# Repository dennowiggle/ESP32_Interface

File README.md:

# ESP32_Interface
Facilitate learning the Z80 Retro! hardware and software.

## Feature list:
ESP32-s3 based board to provide WiFi enabled features.
* RS232 connection to main Z80-Retro console via cable for telnet console access
* RS232 connection to Z80-Retro Aux com port via cable for future WiFi enabled serial download.
* Z80 bus programmer using MCP23S17 SPI IO expander devices.
  - facilitates faster Z80 bus access at 10Mhz SPI rate. 
    - Serial access still relatively slow but 25x I2C.
  - Program Flash without the need for a Raspberry Pi.
  - Might be possible to program areas of SRAM memory e.g. future WiFi file download.
* Off-board SPI using header connection to future board(s) such as FPGA video card.
  - programming FPGA plus additional SPI-FPGA debug features if needed.
* One byte, 8 bit, message register implemented in logic for handshaking with Z80.
  - uses IORQ addreess line 0xA4.
* USB OTG is present in hardware.
* SD card slot for future possiblities.

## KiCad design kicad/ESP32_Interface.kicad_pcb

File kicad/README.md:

# ESP32_Interface
Facilitate learning the Z80 Retro! hardware and software.

## Description
This project adds a WiFi interface to the Z80 Retro! It has been used to facilitate telnet to the Z80 serial port, and programming the Z80 Retro! Flash memory via serial or telnet xmodem or a web interface.

## Top View

## Bottom View

## ESP32 Interface Board Rev 1.0 Release Notes

1. The 'output' directory contains the BOM, netlist, and PDF schematic.

2. Board design used KiCad 7.0.2.

3. Silkscreen box on back side should extend around R501.

4. Holes for U505, the ESP32 module, are tight but it is possible to fit the module in. Larger pin holes would be preferred.

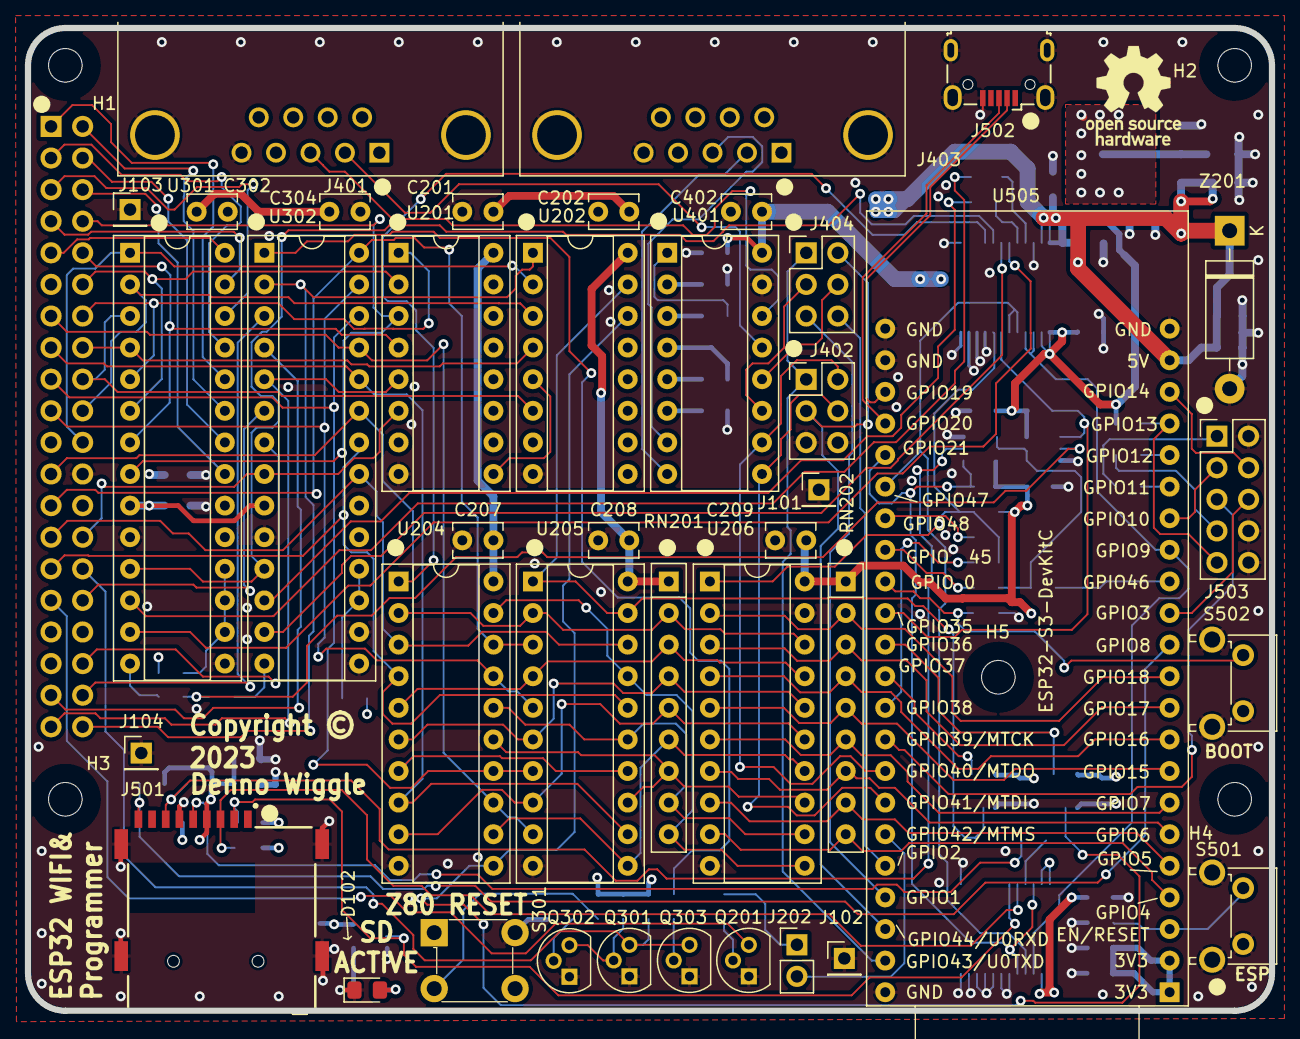
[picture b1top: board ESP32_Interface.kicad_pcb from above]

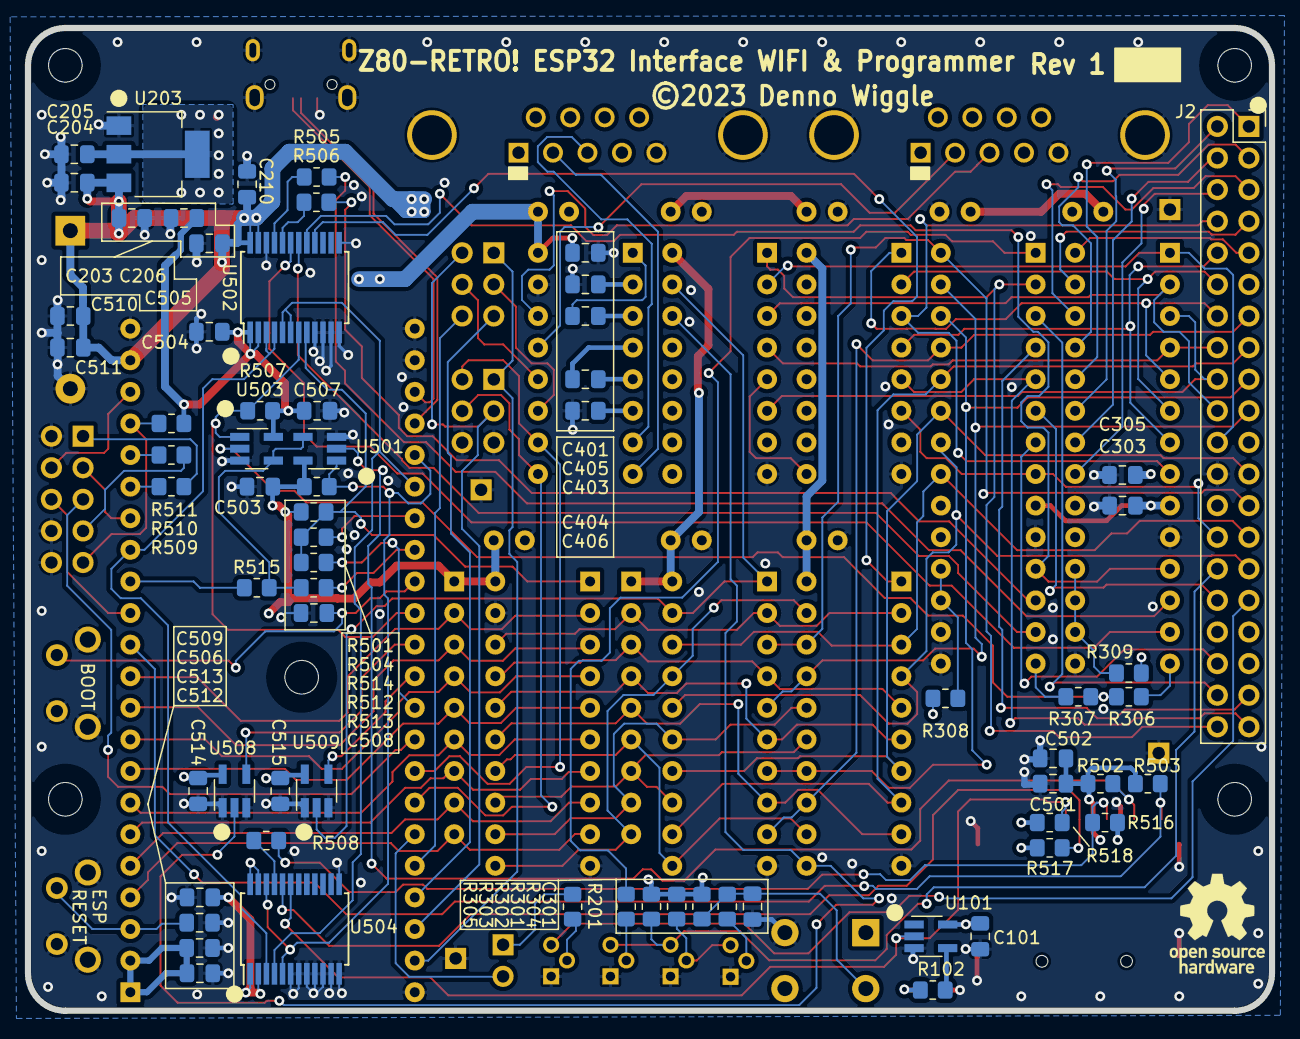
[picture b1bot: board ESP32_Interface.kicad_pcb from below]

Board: 4 copper layers, 100.0 x 79.0 mm, 114 parts (68 on the bottom side), 128 nets.

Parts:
C101, C204, C205, C403, C404, C405, C406, C501, C503, C504, C505, C506, C507, C509, C510, C512, C514, C515: 100nF; C_0805_2012Metric_Pad1.18x1.45mm_HandSolder
C201, C202, C207, C208, C209, C302, C304, C402: 100n; C_Disc_D3.8mm_W2.6mm_P2.50mm
C203, C206, C210, C301, C303, C305, C401, C502, C511, C513: 10uF; C_0805_2012Metric_Pad1.18x1.45mm_HandSolder
C508: DNL; C_0805_2012Metric_Pad1.18x1.45mm_HandSolder
D102: LTST-C170KGKT; LED_0805_2012Metric_Pad1.15x1.40mm_HandSolder
H1, H2, H3, H4, H5: MountingHole; MountingHole_2.7mm_M2.5_DIN965
J2: Conn_02x20_Counter_Clockwise; PinSocket_2x20_P2.54mm_Vertical_clockwise
J101, J102, J103, J104: Conn_01x01; PinHeader_1x01_P2.54mm_Vertical
J202: Conn_01x02; PinHeader_1x02_P2.54mm_Vertical
J401, J403: DB9_Male_MountingHoles; DSUB-9_Male_Horizontal_P2.77x2.84mm_EdgePinOffset7.70mm_Hou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
J402, J404: Conn_02x03; PinHeader_2x03_P2.54mm_Vertical
J501: GCT_MEM2075-00-140-01-A_DP; GCT_MEM2075-00-140-01-A
J502: USB_B_Micro; USB_Micro-B_Wuerth_629105150521
J503: Conn_02x05; PinHeader_2x05_P2.54mm_Vertical
LOGO10, LOGO11: Logo_Open_Hardware_Small; OSHW-Logo_7.5x8mm_SilkScreen
Q201, Q301, Q302, Q303: PN2222; TO-92L
R102, R201, R305: 1K; R_0805_2012Metric_Pad1.20x1.40mm_HandSolder
R301, R302, R303, R308, R309, R501, R502, R503, R504, R507, R511, R516, R517, R518: 10K; R_0805_2012Metric_Pad1.20x1.40mm_HandSolder
R304: 47K; R_0805_2012Metric_Pad1.20x1.40mm_HandSolder
R306, R307, R505, R506, R508, R509, R510: 33R; R_0805_2012Metric_Pad1.20x1.40mm_HandSolder
R512, R513: 0R; R_0805_2012Metric_Pad1.20x1.40mm_HandSolder
R514, R515: DNL; R_0805_2012Metric_Pad1.20x1.40mm_HandSolder
RN201, RN202: 10K; R_Array_SIP9
S301: 1825910-6; Switch_Tactile_THT_6x6mm
S501: 1-1825027-2; SW_Tactile_SPST_Angled_PTS645Vx83-2LFS
S502: 1825027-8; SW_Tactile_SPST_Angled_PTS645Vx83-2LFS
U101: SN74LVC1G04DBVR; SOT-23-5_HandSoldering
U201, U202: 74LS138; DIP-16_W7.62mm_Socket
U203: NCP1117LPST33T3G; SOT-223
U204: 74HC374; DIP-20_W7.62mm_Socket
U205: 74LS244; DIP-20_W7.62mm_Socket
U206: 74LVC245A; DIP-20_W7.62mm_Socket
U301, U302: MCP23S17_SP; DIP-28_W7.62mm_Socket
U401: ICL3232CPZ; DIP-16_W7.62mm_Socket
U501, U503, U508, U509: SN74LVC1G125DBVR; SOT-23-5_HandSoldering
U502, U504: SN74LVC8T245DBR; SSOP-24_5.3x8.2mm_P0.65mm
U505: ESP32-S3-DevKitC
Z201: SA5.0A; D_DO-15_P12.70mm_Horizontal

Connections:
+3.3V: C101.1, C205.1, C206.1, C209.1, C401.1, C402.1, C501.1, C502.1, C503.1, C504.1, C507.1, C509.1, C514.1, C515.1, J501.4 (VDD), R501.1, R502.1, R503.1, R504.1, R507.1, R511.1, R516.1, R517.1, R518.1, RN202.1 (common), U101.5 (VCC), U203.2 (OUT), U203.4 (OUT), U206.20 (Vcc), U401.16 (VCC), U501.5 (VCC), U502.1 (VCCA), U502.2 (DIR), U503.5 (VCC), U504.1 (VCCA), U504.2 (DIR), U504.23 (VCCB), U504.24 (VCCB), U508.5 (VCC), U509.5 (VCC)
+3.3VP: C512.1, C513.1, U505.1 (3V3), U505.2 (3V3)
+5V: C201.1, C202.1, C203.1, C204.1, C207.1, C208.1, C210.1, C302.1, C303.1, C304.1, C305.1, C505.1, C510.1, C511.1, J2.11, R301.1, R302.1, R303.1, R308.1, R309.1, RN201.1 (common), U201.16 (VCC), U202.16 (VCC), U203.3 (IN), U204.20 (VCC), U205.20 (VCC), U301.9 (VDD), U302.9 (VDD), U502.23 (VCCB), U502.24 (VCCB), U505.21 (5V), Z201.1
/ESP32/AUX_DONE: J503.6, U505.13 (GPIO3/ADC1_CH2)
/ESP32/AUX_SPI_CLK: J503.7, R510.2
/ESP32/AUX_SPI_CLK_S: R510.1, U505.18 (GPIO12/ADC2_CH1)
/ESP32/AUX_SPI_MISO: J503.9, R511.2, U505.19 (GPIO13/ADC2_CH2)
/ESP32/AUX_SPI_MOSI: J503.1, R509.2
/ESP32/AUX_SPI_MOSI_S: R509.1, U505.17 (GPIO11/ADC2_CH0)
/ESP32/DATA_DIR_38: R512.1, U505.35 (GPIO38)
/ESP32/DATA_DIR_48: R514.1, U505.29 (GPIO48)
/ESP32/ESP_SD_DET: J501.9 (~DET), R503.2, U505.12 (GPIO8/ADC1_CH7)
/ESP32/ESP_SPI_CLK: U502.3 (A1), U502.4 (A2), U504.3 (A1), U505.15 (GPIO9/ADC1_CH8)
/ESP32/ESP_SPI_MISO: R513.2, R515.2, U501.4 (Y), U503.4 (Y)
/ESP32/ESP_SPI_MISO_IO45: R513.1, U505.30 (GPIO45)
/ESP32/ESP_SPI_MISO_IO46: R515.1, U505.14 (GPIO46)
/ESP32/ESP_SPI_MOSI: U502.5 (A3), U502.6 (A4), U504.4 (A2), U505.28 (GPIO47)
/ESP32/S1ACK: R505.1, U502.21 (B1)
/ESP32/S1BCK: R506.1, U502.20 (B2)
/ESP32/SPI_SD_CLK: J501.5 (CLK), R508.2, R516.2
/ESP32/SPI_SD_MISO: J501.7 (DAT0), R502.2, U501.2 (A)
/ESP32/SPI_SD_MOSI: J501.3 (CMD), R517.2, U504.20 (B2)
/ESP32/SSDCK: R508.1, U504.21 (B1)
/ESP32/USB_OTG_JTAG_D+: J502.3 (D+), U505.26 (GPIO20/USB_D+)
/ESP32/USB_OTG_JTAG_D-: J502.2 (D-), U505.25 (GPIO19/USB_D-)
/ESP32/~AUX_RESET: J503.5, U505.36 (GPIO39/MTCK)
/ESP32/~AUX_SPI_CS0: J503.3, U505.16 (GPIO10/ADC1_CH9)
/ESP32/~AUX_SPI_CS1: J503.4, U505.20 (GPIO14/ADC2_CH3)
/ESP32/~BIORQ_A4_RD: U505.34 (GPIO37), U509.4 (Y)
/ESP32/~BIORQ_A4_WR: U505.33 (GPIO36), U508.4 (Y)
/ESP32/~BOOT: C508.1, S502.1, U505.31 (GPIO0)
/ESP32/~ESP_RESET: C506.1, S501.1, U505.3 (CHIP_PU)
/ESP32/~ESP_SPI_CS0: R501.2, U501.1 (~OE), U504.5 (A3), U504.22 (OE), U505.27 (GPIO21)
/ESP32/~ESP_SPI_CS1: R507.2, U502.7 (A5), U503.1 (~OE), U505.32 (GPIO35)
/RS232/RS232_DOWNLOAD_RX: J401.2, U401.13 (R1IN)
/RS232/RS232_DOWNLOAD_TX: J401.3, U401.14 (T1OUT)
/RS232/RS232_Z80_RX: J403.2, U401.8 (R2IN)
/RS232/RS232_Z80_TX: J403.3, U401.7 (T2OUT)
/RS232/UART01_RX: J404.4, U401.12 (R1OUT)
/RS232/UART01_TX: J404.3, U401.11 (T1IN)
/SPI<->Z80 Bus/ADD_1A: R309.2, U301.16 (A1), U301.17 (A2), U301.18 (~RESET)
/SPI<->Z80 Bus/ADD_1B: R308.2, U302.17 (A2), U302.18 (~RESET)
/SPI<->Z80 Bus/SPI_1A_MISO: R306.1, U301.14 (SO)
/SPI<->Z80 Bus/SPI_1B_MISO: R307.1, U302.14 (SO)
/Z80 Retro Interface/BD0: RN201.2 (R1), U204.2 (O0), U205.2 (I0a), U206.18 (B1)
/Z80 Retro Interface/BD1: RN201.3 (R2), U204.5 (O1), U205.4 (I1a), U206.17 (B2)
/Z80 Retro Interface/BD2: RN201.4 (R3), U204.6 (O2), U205.6 (I2a), U206.16 (B3)
/Z80 Retro Interface/BD3: RN201.5 (R4), U204.9 (O3), U205.8 (I3a), U206.15 (B4)
/Z80 Retro Interface/BD4: RN201.6 (R5), U204.12 (O4), U205.11 (I0b), U206.14 (B5)
/Z80 Retro Interface/BD5: RN201.7 (R6), U204.15 (O5), U205.13 (I1b), U206.13 (B6)
/Z80 Retro Interface/BD6: RN201.8 (R7), U204.16 (O6), U205.15 (I2b), U206.12 (B7)
/Z80 Retro Interface/BD7: RN201.9 (R8), U204.19 (O7), U205.17 (I3b), U206.11 (B8)
/Z80 Retro Interface/~INT: J2.16, Q201.3 (C)
/Z80 Retro Interface/~IORQ_AX: U201.9 (O6), U202.5 (E2)
A0: J2.30, U202.2 (A1), U301.1 (GPB0)
A1: J2.31, U202.3 (A2), U301.2 (GPB1)
A2: J2.32, U202.6 (E3), U301.3 (GPB2)
A3: J2.33, U202.4 (E1), U301.4 (GPB3)
A4: J2.34, U201.1 (A0), U301.5 (GPB4)
A5: J2.35, U201.2 (A1), U301.6 (GPB5)
A6: J2.36, U201.4 (E1), U301.7 (GPB6)
A7: J2.37, U201.3 (A2), U301.8 (GPB7)
A8: J2.38, U301.21 (GPA0)
A9: J2.39, U301.22 (GPA1)
A10: J2.40, U301.23 (GPA2)
A11: J2.1, U301.24 (GPA3)
A12: J2.2, U301.25 (GPA4)
A13: J2.3, U301.26 (GPA5)
A14: J2.4, U301.27 (GPA6)
A15: J2.5, U301.28 (GPA7)
D0: J2.14, U204.3 (D0), U205.18 (O0a), U302.21 (GPA0)
D1: J2.15, U204.4 (D1), U205.16 (O1a), U302.22 (GPA1)
D2: J2.12, U204.7 (D2), U205.14 (O2a), U302.23 (GPA2)
D3: J2.8, U204.8 (D3), U205.12 (O3a), U302.24 (GPA3)
D4: J2.7, U204.13 (D4), U205.9 (O0b), U302.25 (GPA4)
D5: J2.9, U204.14 (D5), U205.7 (O1b), U302.26 (GPA5)
D6: J2.10, U204.17 (D6), U205.5 (O2b), U302.27 (GPA6)
D7: J2.13, U204.18 (D7), U205.3 (O3b), U302.28 (GPA7)
ESP_D0: RN202.2 (R1), U206.2 (A1), U505.11 (GPIO18/ADC2_CH7)
ESP_D1: RN202.3 (R2), U206.3 (A2), U505.10 (GPIO17/ADC2_CH6)
ESP_D2: RN202.4 (R3), U206.4 (A3), U505.9 (GPIO16/ADC2_CH5/32K_N)
ESP_D3: RN202.5 (R4), U206.5 (A4), U505.8 (GPIO15/ADC2_CH4/32K_P)
ESP_D4: RN202.6 (R5), U206.6 (A5), U505.7 (GPIO7/ADC1_CH6)
ESP_D5: RN202.7 (R6), U206.7 (A6), U505.6 (GPIO6/ADC1_CH5)
ESP_D6: RN202.8 (R7), U206.8 (A7), U505.5 (GPIO5/ADC1_CH4)
ESP_D7: RN202.9 (R8), U206.9 (A8), U505.4 (GPIO4/ADC1_CH3)
ESP_DATA_DIR5_W: U204.1 (OE), U502.16 (B6)
ESP_DATA_DIR_W: R504.2, R512.2, R514.2, U206.1 (DIR), U502.8 (A6)
GND: C101.2, C201.2, C202.2, C203.2, C204.2, C205.2, C206.2, C207.2, C208.2, C209.2, C210.2, C301.2, C302.2, C303.2, C304.2, C305.2, C401.2, C402.2, C405.2, C406.2, C501.2, C502.2, C503.2, C504.2, C505.2, C506.2, C507.2, C508.2, C509.2, C510.2, C511.2, C512.2, C513.2, C514.2, C515.2, D102.1, J2.29, J101.1, J102.1, J103.1, J104.1, J401.0 (PAD), J401.5, J402.5, J402.6, J403.0 (PAD), J403.5, J501.6 (VSS), J501.SH1 (SHIELD), J501.SH2 (SHIELD), J501.SH3 (SHIELD), J501.SH4 (SHIELD), J502.5 (GND), J502.6 (Shield), J503.2, J503.8, J503.10, Q201.1 (E), Q301.1 (E), Q302.1 (E), Q303.1 (E), S301.2, S501.2, S501.SH1, S501.SH2, S502.2, S502.SH1, S502.SH2, U101.3 (GND), U201.8 (GND), U202.8 (GND), U203.1 (ADJ/GND), U204.10 (GND), U205.10 (GND), U206.10 (GND), U206.19 (OE), U301.10 (VSS), U301.15 (A0), U302.10 (VSS), U302.15 (A0), U302.16 (A1), U401.15 (GND), U501.3 (GND), U502.9 (A7), U502.10 (A8), U502.11 (GND), U502.12 (GND), U502.13 (GND), U502.22 (OE), U503.3 (GND), U504.6 (A4), U504.7 (A5), U504.8 (A6), U504.9 (A7), U504.10 (A8), U504.11 (GND), U504.12 (GND), U504.13 (GND), U505.22 (GND), U505.23 (GND), U505.24 (GND), U505.44 (GND), U508.1 (~OE), U508.3 (GND), U509.1 (~OE), U509.3 (GND), Z201.2
unnamed: C301.1, R301.2, R304.1, S301.3
unnamed: D102.2, R102.2
unnamed: J202.1, R201.2
unnamed: Q201.2 (B), R201.1
unnamed: Q301.2 (B), Q302.3 (C), R302.2
unnamed: Q302.2 (B), R304.2
unnamed: Q303.2 (B), R305.2
unnamed: R102.1, U101.4 (Y)
unnamed: R305.1, U302.1 (GPB0)
unnamed: C403.2, U401.1 (C1+)
unnamed: C403.1, U401.3 (C1-)
unnamed: C404.1, U401.4 (C2+)
unnamed: C404.2, U401.5 (C2-)
unnamed: C405.1, U401.2 (VS+)
unnamed: C406.1, U401.6 (VS-)
SPI_1A_CLK: R505.2, U301.12 (SCK)
SPI_1A_MOSI: U301.13 (SI), U502.19 (B3)
SPI_1B_CLK: R506.2, U302.12 (SCK)
SPI_1B_MOSI: U302.13 (SI), U502.18 (B4)
SPI_1_MISO: R306.2, R307.2, U503.2 (A)
SPI_CS1: U301.11 (~CS), U302.11 (~CS), U502.17 (B5)
UART0_RX: J402.3, J404.2, U505.42 (GPIO44/U0RXD)
UART0_TX: J402.1, J404.1, U505.43 (GPIO43/U0TXD)
UART1_RX: J404.6, U505.40 (GPIO2/ADC1_CH1)
UART1_TX: J404.5, U505.41 (GPIO1/ADC1_CH0)
UART2_RX: J402.4, U401.9 (R2OUT), U505.38 (GPIO41/MTDI)
UART2_TX: J402.2, U401.10 (T2IN), U505.37 (GPIO40/MTDO)
Z80_INT: J202.2, U505.39 (GPIO42/MTMS)
~BUSACK: J2.23, U302.7 (GPB6)
~BUSRQ: J2.25, U302.6 (GPB5)
~IORQ_A4_RD: U202.15 (O0), U205.1 (OEa), U205.19 (OEb), U509.2 (A)
~IORQ_A4_WR: U202.14 (O1), U204.11 (Cp), U508.2 (A)
~IORQ: J2.20, U201.5 (E2), U302.5 (GPB4)
~M1: J2.27, U201.6 (E3), U302.8 (GPB7)
~MREQ: J2.19, U302.4 (GPB3)
~RD: J2.21, U202.1 (A0), U302.2 (GPB1)
~RESET: J2.26, Q301.3 (C), Q303.3 (C), R303.2
~SPI_SD_CS0: J501.2 (DAT3/CD), R518.2, U101.2 (A), U504.19 (B3)
~WR: J2.22, U302.3 (GPB2)

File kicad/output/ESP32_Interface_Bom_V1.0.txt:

# ESP32_Interface.kicad_sch

## 6/12/2023 5:54:20 PM

## Eeschema 7.0.2

## Component Count:112

Ref | Qty | Value | Digikey | Datasheet | Description
----|-----|-------|---------|-----------|------------
C101, C204, C205, C403, C404, C405, C406, C501, C503, C504, C505, C506, C507, C509, C510, C512, C514, C515 | 18 | 100nF | 732-8045-1-ND | https://www.we-online.com/katalog/datasheet/885012207045.pdf | Unpolarized capacitor, small symbol
C201, C202, C207, C208, C209, C302, C304, C402 | 8 | 100n | 399-9859-1-ND‎ | https://api.kemet.com/component-edge/download/specsheet/C315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 | Unpolarized capacitor, small symbol
C203, C206, C210, C301, C303, C305, C401, C502, C511, C513 | 10 | 10uF | 1276-6455-1-ND | https://media.digikey.com/pdf/Data%20Sheets/Samsung%20PDFs/C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 | Unpolarized capacitor, small symbol
C508 | 1 | DNL | 732-8045-1-ND | https://www.we-online.com/katalog/datasheet/885012207045.pdf | Unpolarized capacitor, small symbol
D102 | 1 | LTST-C170KGKT | 160-1414-1-ND | https://optoelectronics.liteon.com/upload/download/DS22-2000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 | LED RED CLEAR SMD
H1, H2, H3, H4, H5 | 5 | MountingHole |  | ~ | Mounting Hole without connection
J2 | 1 | Conn_02x20_Counter_Clockwise |  | https://www.amazon.com/gp/product/B084Q4W1PW/ref=ppx_yo_dt_b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 | Generic connector, double row, 02x20, counter clockwise pin numbering scheme (similar to DIP package numbering), script generated (kicad-library-utils/schlib/autogen/connector/)
J101, J102, J103, J104 | 4 | Conn_01x01 |  | ~ | Generic connector, single row, 01x01, script generated (kicad-library-utils/schlib/autogen/connector/)
J202 | 1 | Conn_01x02 | 2057-PH1-02-UA-ND | https://app.adam-tech.com/products/download/data_sheet/20160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 | Generic connector, single row, 01x02, script generated (kicad-library-utils/schlib/autogen/connector/)
J401, J403 | 2 | DB9_Male_MountingHoles | AE10970-ND | http://www.assmann-wsw.com/uploads/datasheets/ASS_4888_CO.pdf | 
J402, J404 | 2 | Conn_02x03 | 2057-PH2-06-UA-ND | https://app.adam-tech.com/products/download/data_sheet/20206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 | Generic connector, double row, 02x03, odd/even pin numbering scheme (row 1 odd numbers, row 2 even numbers), script generated (kicad-library-utils/schlib/autogen/connector/)
J501 | 1 | GCT_MEM2075-00-140-01-A_DP | 2073-MEM2075-00-140-01-ACT-ND | https://gct.co/files/specs/mem2075-spec.pdf | 
J502 | 1 | USB_B_Micro | 732-5960-1-ND | https://www.we-online.com/components/products/datasheet/6291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 | USB Micro Type B connector
J503 | 1 | Conn_02x05_Right_Angle | 2057-PH2RA-10-UA-ND | https://app.adam-tech.com/products/download/data_sheet/20050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 | Generic connector, double row, 02x05, odd/even pin numbering scheme (row 1 odd numbers, row 2 even numbers), script generated (kicad-library-utils/schlib/autogen/connector/)
Q201, Q301, Q302, Q303 | 4 | PN2222 | 1514-PN2222APBFREE-ND | https://my.centralsemi.com/datasheets/PN2221-2222A.PDF | NPN transistor, emitter/base/collector
R102, R201, R305 | 3 | 1K | 311-1.0KARCT-ND | https://www.yageo.com/upload/media/product/productsearch/dat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 | Resistor, US symbol
R301, R302, R303, R308, R309, R501, R502, R503, R504, R507, R511, R516, R517, R518 | 14 | 10K | 311-10KARCT-ND | https://www.yageo.com/upload/media/product/productsearch/dat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 | Resistor, US symbol
R304 | 1 | 47K | 311-47KARCT-ND | https://www.yageo.com/upload/media/product/productsearch/dat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 | Resistor, US symbol
R306, R307, R505, R506, R508, R509, R510 | 7 | 33R | 311-33ARCT-ND | https://www.yageo.com/upload/media/product/productsearch/dat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 | Resistor, US symbol
R512, R513 | 2 | 0R | 311-0.0ARCT-ND | https://www.yageo.com/upload/media/product/productsearch/dat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 | Resistor, US symbol
R514, R515 | 2 | DNL | 311-0.0ARCT-ND | https://www.yageo.com/upload/media/product/productsearch/dat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 | Resistor, US symbol
RN201, RN202 | 2 | 10K | 4609X-101-103LF-ND | https://www.bourns.com/docs/Product-Datasheets/4600x.pdf | 8 resistor network, star topology, bussed resistors, small symbol
S301 | 1 | 1825910-6 | 450-1650-ND | https://www.te.com/commerce/DocumentDelivery/DDEController?A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 | SWITCH TACTILE SPST-NO 0.05A 24V
S501 | 1 | 1-1825027-2 | 1-1825027-2-ND | https://www.te.com/commerce/DocumentDelivery/DDEController?A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 | SWITCH TACTILE SPST-NO 0.05A 24V
S502 | 1 | 1825027-8 | 450-1657-ND | https://www.te.com/commerce/DocumentDelivery/DDEController?A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 | SWITCH TACTILE SPST-NO 0.05A 24V
U101 | 1 | SN74LVC1G04DBVR | 296-11599-1-ND | http://www.ti.com/general/docs/suppproductinfo.tsp?distId=10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 | IC INVERTER 1CH 1-INP SOT23-5
U201, U202 | 2 | 74LS138 | 296-1728-5-ND | http://www.ti.com/lit/gpn/sn74LS138 | Decoder 3 to 8 active low outputs
U203 | 1 | NCP1117LPST33T3G | NCP1117LPST33T3GOSCT-ND | https://www.onsemi.com/pdf/datasheet/ncp1117lp-d.pdf | IC REG LINEAR 3.3V 1A SOT223
U204 | 1 | 74HC374 | 296-12806-5-ND | https://www.ti.com/lit/ds/symlink/cd74hct374.pdf | 8-bit Register, 3-state outputs
U205 | 1 | 74LS244 | 296-1653-5-ND | https://www.ti.com/lit/ds/symlink/sn74ls241.pdf | Octal Buffer and Line Driver With 3-State Output, active-low enables, non-inverting outputs
U206 | 1 | 74LVC245A | 296-8503-5-ND | http://www.ti.com/lit/ds/symlink/sn74lvc245a.pdf | Octal BUS Transceivers, 3-State outputs
U301, U302 | 2 | MCP23S17_SP | MCP23S17-E/SP-ND | http://ww1.microchip.com/downloads/en/DeviceDoc/20001952C.pdf | 16-bit I/O expander, SPI, interrupts, w pull-ups, SPDIP-28
U401 | 1 | ICL3232CPZ | ICL3232CPZ-ND‎ | https://www.renesas.com/us/en/document/dst/icl3221-icl3222-i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 | 3.0V to 5.5V, Low-Power, up to 1Mbps, True RS-232 Transceivers Using Four 0.1μF External Capacitors
U501, U503, U508, U509 | 4 | SN74LVC1G125DBVR | 296-11603-1-ND | http://www.ti.com/general/docs/suppproductinfo.tsp?distId=10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 | IC BUF NON-INVERT 5.5V SOT23-5
U502, U504 | 2 | SN74LVC8T245DBR | 296-21065-1-ND | https://www.ti.com/lit/ds/symlink/sn74lvc8t245.pdf | Octal BUS Transceivers, 3-State outputs
U505 | 1 | ESP32-S3-DevKitC | 1965-ESP32-S3-DEVKITC-1-N8R2-ND | https://docs.espressif.com/projects/esp-idf/en/latest/esp32s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 | ESP32-S3-DevKitC
Z201 | 1 | SA5.0A | SA5.0ALFCT-ND | https://www.littelfuse.com/~/media/electronics/datasheets/tv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 | TVS DIODE 5VWM 9.2VC DO214AA

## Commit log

2023-07-31 Update README.md
    First Commit
2023-07-31 Initial Board Release commit.
2023-07-31 Update README.md
    Cost saving note added
2023-07-31 Initial Release
2023-07-31 Updated notes on schematic PDF.
2024-12-19 Add the gerbers
2024-12-19 Initial release of SW
2024-12-19 Update README file.
2024-12-19 Updated Documentation
2024-12-19 Updated Comments

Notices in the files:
kicad/ESP32_Interface.kicad_pcb:
©2023
Copyright ©
